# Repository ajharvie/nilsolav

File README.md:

# Nils Olav
A simple-to-build, low-profile, ortholinear keyboard named after a [famous penguin.](https://en.wikipedia.org/wiki/Nils_Olav) This keyboard is based around the Elite-C v4. It features a left-sided numpad, (useful for design work), 2U spacebar, a cute little penguin, and as low a parts count as possible to make it easy for individuals to build with very simple soldering tools.

[A pre-compiled firmware hex](firmware/nilsolav_default.hex) (nilsolav_default.hex) is provided for my slightly unusual default keymap ([shown here](firmware/nilsolav/keymaps/default/keymap.c)). QMK users who wish to build their own keymap can do so using the source code provided in the [firmware](firmware) folder.

In the default keymap, double-tapping the numlock key toggles a layer where the numpad is transformed into a nav cluster.

Parts needed:
* PCB x1
* Bottom plate x1 
* Top plate x1 (1.5 mm thick)
* 8mm M2 standoffs x7
* M2 screws x14 (length depends on bottom plate thickness)
* Elite C v4 x1
* 2U stabiliser x1
* SOD-123 SMD diodes x77
* Your choice of MX switches x77
* Keycaps

[A build guide is included here.](doc/buildguide.md)

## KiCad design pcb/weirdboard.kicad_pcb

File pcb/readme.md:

KiCad files and gerbers for the keyboard. If you just want to make the keyboard PCBs, you just need the .zip of gerbers. If you're going to edit the PCB files, you'll need the following libraries:

ai03's MX footprint libary: https://github.com/ai03-2725/MX_Alps_Hybrid
Keebio-parts: https://github.com/keebio/Keebio-Parts.pretty
ai03's random-keyboard-parts: https://github.com/ai03-2725/random-keyboard-parts.pretty

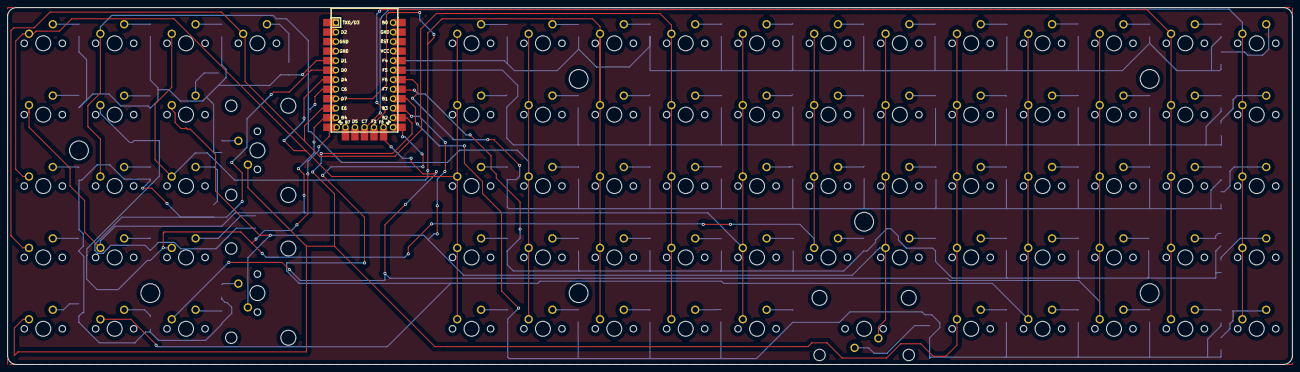
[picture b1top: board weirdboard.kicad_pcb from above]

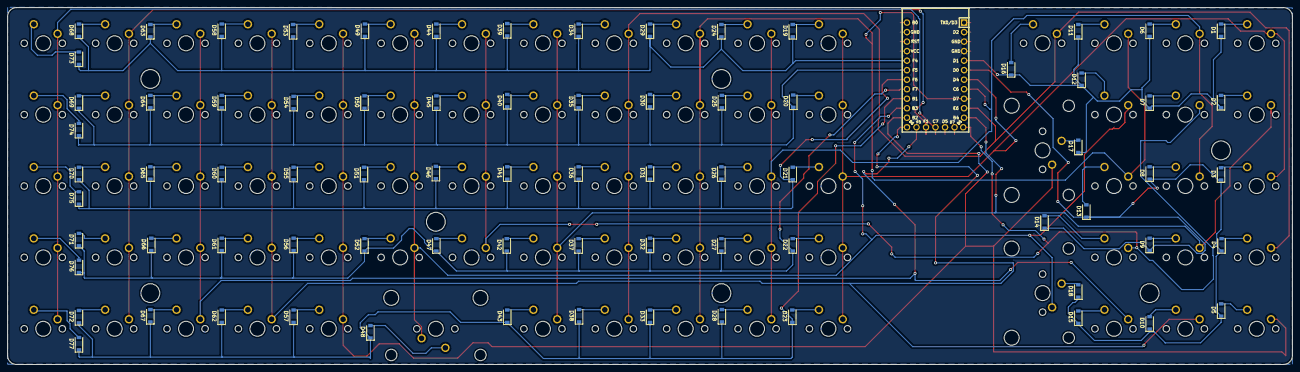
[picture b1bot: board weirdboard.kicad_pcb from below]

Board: 2 copper layers, 342.9 x 95.3 mm, 155 parts (77 on the bottom side), 97 nets.

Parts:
D1, D2, D3, D4, D5, D6, D7, D8, D9, D10, D11, D12, D13, D14, D15, D16, D17, D18, D19, D20, D21, D22, D23, D24, D25, D26, D27, D28, D29, D30, D31, D32, D33, D34, D35, D36, D37, D38, D39, D40, D41, D42, D43, D44, D45, D46, D47, D48, D49, D50, D51, D52, D53, D54, D55, D56, D57, D58, D59, D60, D61, D62, D63, D64, D65, D66, D67, D68, D69, D70, D71, D72, D73, D74, D75, D76, D77: D_Small; D_SOD-123
MX1, MX2, MX3, MX4, MX5, MX6, MX7, MX8, MX9, MX10, MX11, MX12, MX13, MX14, MX15, MX16, MX19, MX20, MX21, MX22, MX23, MX24, MX25, MX26, MX27, MX28, MX29, MX30, MX31, MX32, MX33, MX34, MX35, MX36, MX37, MX38, MX39, MX40, MX41, MX42, MX43, MX44, MX45, MX46, MX47, MX49, MX50, MX51, MX52, MX53, MX54, MX55, MX56, MX57, MX58, MX59, MX60, MX61, MX62, MX63, MX64, MX65, MX66, MX67, MX68, MX69, MX70, MX71, MX72, MX73, MX74, MX75, MX76, MX77: MX-NoLED; MXOnly-1U-NoLED
MX17, MX18, MX48: MX-NoLED; MXOnly-2U-NoLED
U1: Elite-C; Elite-C-castellated-29pin-holes

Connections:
unnamed: D1.2, MX1.2
unnamed: D2.2, MX2.2
unnamed: D3.2, MX3.2
unnamed: D4.2, MX4.2
unnamed: D5.2, MX5.2
unnamed: D6.2, MX6.2
unnamed: D7.2, MX7.2
unnamed: D8.2, MX8.2
unnamed: D9.2, MX9.2
unnamed: D10.2, MX10.2
unnamed: D11.2, MX11.2
unnamed: D12.2, MX12.2
unnamed: D13.2, MX13.2
unnamed: D14.2, MX14.2
unnamed: D15.2, MX15.2
unnamed: D16.2, MX16.2
unnamed: D17.2, MX17.2
unnamed: D18.2, MX18.2
unnamed: D19.2, MX19.2
unnamed: D20.2, MX20.2
unnamed: D21.2, MX21.2
unnamed: D22.2, MX22.2
unnamed: D23.2, MX23.2
unnamed: D24.2, MX24.2
unnamed: D25.2, MX25.2
unnamed: D26.2, MX26.2
unnamed: D27.2, MX27.2
unnamed: D28.2, MX28.2
unnamed: D29.2, MX29.2
unnamed: D30.2, MX30.2
unnamed: D31.2, MX31.2
unnamed: D32.2, MX32.2
unnamed: D33.2, MX33.2
unnamed: D34.2, MX34.2
unnamed: D35.2, MX35.2
unnamed: D36.2, MX36.2
unnamed: D37.2, MX37.2
unnamed: D38.2, MX38.2
unnamed: D39.2, MX39.2
unnamed: D40.2, MX40.2
unnamed: D41.2, MX41.2
unnamed: D42.2, MX42.2
unnamed: D43.2, MX43.2
unnamed: D44.2, MX44.2
unnamed: D45.2, MX45.2
unnamed: D46.2, MX46.2
unnamed: D47.2, MX47.2
unnamed: D48.2, MX48.2
unnamed: D49.2, MX49.2
unnamed: D50.2, MX50.2
unnamed: D51.2, MX51.2
unnamed: D52.2, MX52.2
unnamed: D53.2, MX53.2
unnamed: D54.2, MX54.2
unnamed: D55.2, MX55.2
unnamed: D56.2, MX56.2
unnamed: D57.2, MX57.2
unnamed: D58.2, MX58.2
unnamed: D59.2, MX59.2
unnamed: D60.2, MX60.2
unnamed: D61.2, MX61.2
unnamed: D62.2, MX62.2
unnamed: D63.2, MX63.2
unnamed: D64.2, MX64.2
unnamed: D65.2, MX65.2
unnamed: D66.2, MX66.2
unnamed: D67.2, MX67.2
unnamed: D68.2, MX68.2
unnamed: D69.2, MX69.2
unnamed: D70.2, MX70.2
unnamed: D71.2, MX71.2
unnamed: D72.2, MX72.2
unnamed: D73.2, MX73.2
unnamed: D74.2, MX74.2
unnamed: D75.2, MX75.2
unnamed: D76.2, MX76.2
unnamed: D77.2, MX77.2
col0: MX1.1, MX3.1, MX19.1, MX20.1, MX21.1, MX22.1, MX23.1, U1.7
col1: MX6.1, MX8.1, MX24.1, MX25.1, MX26.1, MX27.1, MX28.1, U1.8
col2: MX11.1, MX13.1, MX29.1, MX30.1, MX31.1, MX32.1, MX33.1, U1.9
col3: MX4.1, MX16.1, MX34.1, MX35.1, MX36.1, MX37.1, MX38.1, U1.10
col4: MX2.1, MX9.1, MX39.1, MX40.1, MX41.1, MX42.1, MX43.1, U1.11
col5: MX7.1, MX14.1, MX44.1, MX45.1, MX46.1, MX47.1, U1.12
col6: MX12.1, MX18.1, MX48.1, MX49.1, MX50.1, MX51.1, MX52.1, U1.15
col7: MX5.1, MX17.1, MX53.1, MX54.1, MX55.1, MX56.1, MX57.1, U1.14
col8: MX10.1, MX58.1, MX59.1, MX60.1, MX61.1, MX62.1, U1.13
col9: MX15.1, MX63.1, MX64.1, MX65.1, MX66.1, MX67.1, U1.29
col10: MX68.1, MX69.1, MX70.1, MX71.1, MX72.1, U1.28
col11: MX73.1, MX74.1, MX75.1, MX76.1, MX77.1, U1.27
gnd: U1.3, U1.4
row0: D19.1, D24.1, D29.1, D34.1, D39.1, D44.1, D49.1, D53.1, D58.1, D63.1, D68.1, D73.1, U1.20
row1: D20.1, D25.1, D30.1, D35.1, D40.1, D45.1, D50.1, D54.1, D59.1, D64.1, D69.1, D74.1, U1.19
row2: D21.1, D26.1, D31.1, D36.1, D41.1, D46.1, D51.1, D55.1, D60.1, D65.1, D70.1, D75.1, U1.18
row3: D22.1, D27.1, D32.1, D37.1, D42.1, D47.1, D52.1, D56.1, D61.1, D66.1, D71.1, D76.1, U1.17
row4: D23.1, D28.1, D33.1, D38.1, D43.1, D48.1, D57.1, D62.1, D67.1, D72.1, D77.1, U1.16
row5: D1.1, D2.1, D6.1, D7.1, D11.1, D12.1, D16.1, D17.1, U1.5
row6: D3.1, D4.1, D5.1, D8.1, D9.1, D10.1, D13.1, D14.1, D15.1, D18.1, U1.6

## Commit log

2021-03-24 added images
2021-03-24 added firmware
2022-01-21 added licence
    MIT licence added
2025-10-30 fix path
